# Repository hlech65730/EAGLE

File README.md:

# EAGLE
CAD Repository for PCB Design
- Raspberry Reansas Add On - RRAO1

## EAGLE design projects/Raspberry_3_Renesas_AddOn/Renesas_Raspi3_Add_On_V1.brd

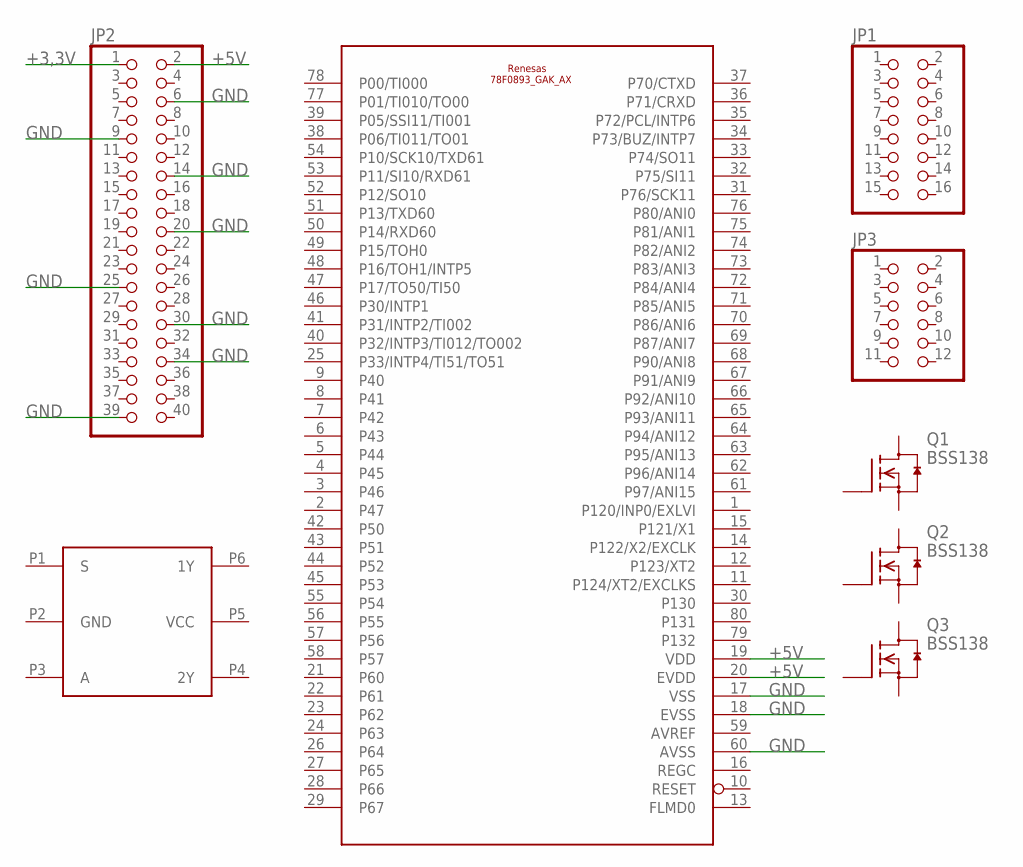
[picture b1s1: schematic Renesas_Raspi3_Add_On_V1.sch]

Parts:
74LVC1G18: 74LVC1G18
78F0893: 78F0893_GAK_AX; LQFP80
JP1: PINHD-2X8; 2X08
JP2: PINHD-2X20; 2X20
JP3: PINHD-2X6; 2X06
Q1, Q2, Q3: BSS138; SOT23

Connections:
+3,3V: JP2.1
+5V: 78F0893.19 (VDD), 78F0893.20 (EVDD), JP2.2
AVREF: 78F0893.59 (AVREF)
GND: 78F0893.17 (VSS), 78F0893.18 (EVSS), 78F0893.60 (AVSS), JP2.6, JP2.9, JP2.14, JP2.20, JP2.25, JP2.30, JP2.34, JP2.39

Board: 2 copper layers, 8 parts (0 on the bottom side), 2 nets, no tracks yet.

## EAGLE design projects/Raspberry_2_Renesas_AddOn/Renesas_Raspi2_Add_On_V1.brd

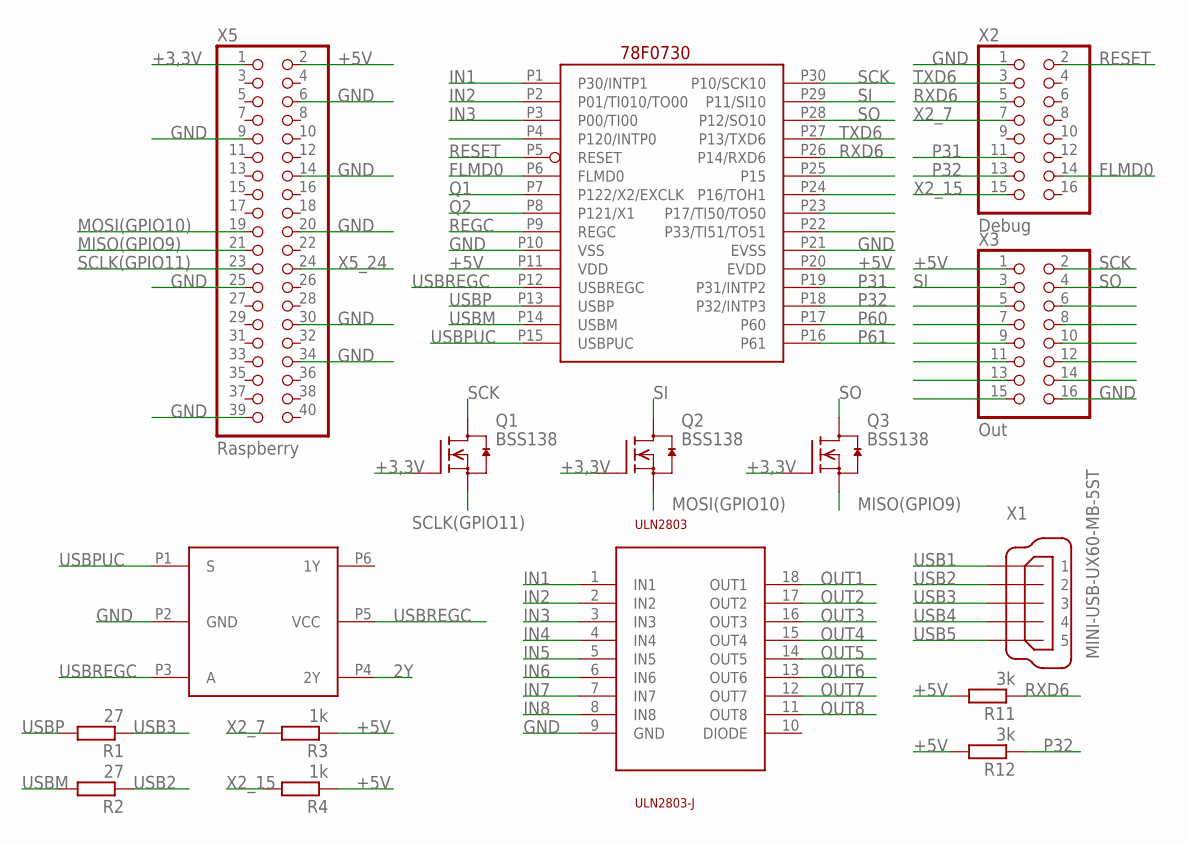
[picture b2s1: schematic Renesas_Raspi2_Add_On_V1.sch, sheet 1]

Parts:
Q1, Q2, Q3: BSS138; SOT23
R1, R2: 27; R0603
R3, R4: 1k; R0603
R11, R12: 3k; R0603
U$1: 78F0730_CAB_AX; SSOP30
U$2: 74LVC1G18
ULN2803: ULN2803-J; SOJ18-45
X1: MINI-USB-UX60-MB-5ST; UX60-MB-5ST
X2: Debug; 2X08
X3: Out; 2X08
X5: Raspberry; 2X20

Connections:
2Y: U$2.P4 (2Y); also elsewhere on the board
+3,3V: Q1.1 (G), Q2.1 (G), Q3.1 (G), X5.1; also elsewhere on the board
+5V: R3.1, R4.1, R11.2, R12.2, U$1.P11 (VDD), U$1.P20 (EVDD), X3.1, X5.2; also elsewhere on the board
FLMD0: U$1.P6 (FLMD0), X2.14
GND: U$1.P10 (VSS), U$1.P21 (EVSS), U$2.P2 (GND), ULN2803.9 (GND), X2.1, X3.16, X5.6, X5.9, X5.14, X5.20, X5.25, X5.30, X5.34, X5.39; also elsewhere on the board
IN1: U$1.P1 (P30/INTP1), ULN2803.1 (IN1)
IN2: U$1.P2 (P01/TI010/TO00), ULN2803.2 (IN2)
IN3: U$1.P3 (P00/TI00), ULN2803.3 (IN3)
IN4: ULN2803.4 (IN4)
IN5: ULN2803.5 (IN5)
IN6: ULN2803.6 (IN6)
IN7: ULN2803.7 (IN7)
IN8: ULN2803.8 (IN8)
MISO(GPIO9): Q3.2 (S), X5.21; also elsewhere on the board
MOSI(GPIO10): Q2.2 (S), X5.19; also elsewhere on the board
OUT1: ULN2803.18 (OUT1)
OUT2: ULN2803.17 (OUT2)
OUT3: ULN2803.16 (OUT3)
OUT4: ULN2803.15 (OUT4)
OUT5: ULN2803.14 (OUT5)
OUT6: ULN2803.13 (OUT6)
OUT7: ULN2803.12 (OUT7)
OUT8: ULN2803.11 (OUT8)
P31: U$1.P19 (P31/INTP2), X2.11
P32: R12.1, U$1.P18 (P32/INTP3), X2.13
P60: U$1.P17 (P60); also elsewhere on the board
P61: U$1.P16 (P61); also elsewhere on the board
Q1: U$1.P7 (P122/X2/EXCLK); also elsewhere on the board
Q2: U$1.P8 (P121/X1); also elsewhere on the board
REGC: U$1.P9 (REGC); also elsewhere on the board
RESET: U$1.P5 (RESET), X2.2; also elsewhere on the board
RXD6: R11.1, U$1.P26 (P14/RXD6), X2.5
SCK: Q1.3 (D), U$1.P30 (P10/SCK10), X3.2; also elsewhere on the board
SCLK(GPIO11): Q1.2 (S), X5.23; also elsewhere on the board
SI: Q2.3 (D), U$1.P29 (P11/SI10), X3.3; also elsewhere on the board
SO: Q3.3 (D), U$1.P28 (P12/SO10), X3.4; also elsewhere on the board
TXD6: U$1.P27 (P13/TXD6), X2.3
USB1: X1.1
USB2: R2.1, X1.2
USB3: R1.1, X1.3; also elsewhere on the board
USB4: X1.4
USB5: X1.5
USBM: R2.2, U$1.P14 (USBM)
USBP: R1.2, U$1.P13 (USBP)
USBPUC: U$1.P15 (USBPUC), U$2.P1 (S)
USBREGC: U$1.P12 (USBREGC), U$2.P3 (A), U$2.P5 (VCC); also elsewhere on the board
X2_7: R3.2, X2.7
X2_15: R4.2, X2.15; also elsewhere on the board
X5_24: X5.24; also elsewhere on the board

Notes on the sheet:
78F0730

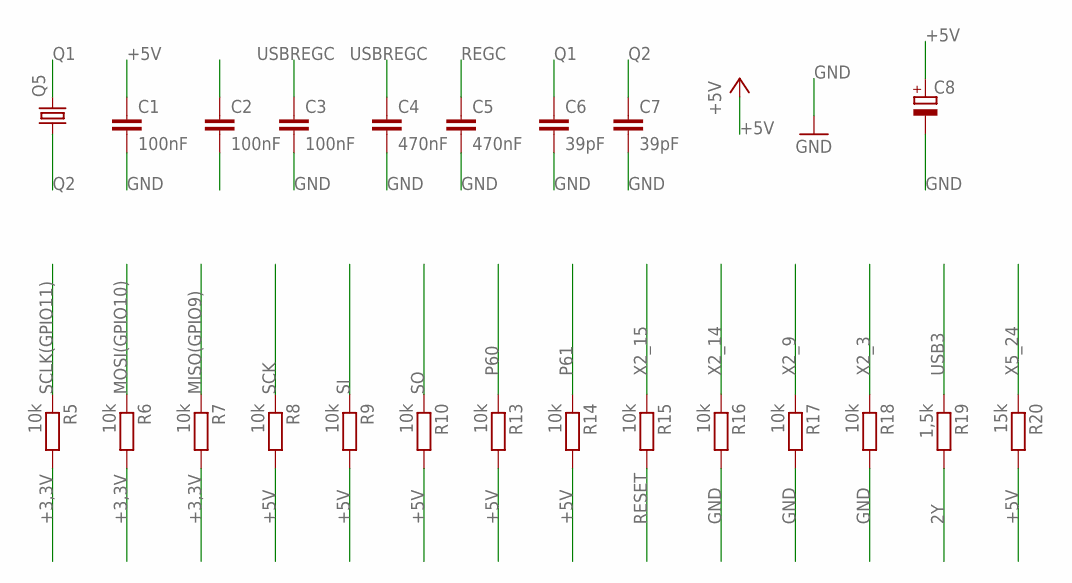
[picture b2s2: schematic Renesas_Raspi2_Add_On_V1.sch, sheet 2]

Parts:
C1, C2, C3: 100nF; C0603
C4, C5: 470nF; C0603
C6, C7: 39pF; C0603
C8: CPOL-EUSANYO_SMD_F8; SANYO-OSCON_SMD_F8
Q5: CRYSTALHC49UP; HC49UP
R5, R6, R7, R8, R9, R10, R13, R14, R15, R16, R17, R18: 10k; R0603
R19: 1,5k; R0603
R20: 15k; R0603

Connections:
2Y: R19.2; also elsewhere on the board
+3,3V: R5.2, R6.2, R7.2; also elsewhere on the board
+5V: C1.1, C8.+, R8.2, R9.2, R10.2, R13.2, R14.2, R20.2; also elsewhere on the board
GND: C1.2, C3.2, C4.2, C5.2, C6.2, C7.2, C8.-, R16.2, R17.2, R18.2; also elsewhere on the board
MISO(GPIO9): R7.1; also elsewhere on the board
MOSI(GPIO10): R6.1; also elsewhere on the board
P60: R13.1; also elsewhere on the board
P61: R14.1; also elsewhere on the board
Q1: C6.1, Q5.2; also elsewhere on the board
Q2: C7.1, Q5.1; also elsewhere on the board
REGC: C5.1; also elsewhere on the board
RESET: R15.2; also elsewhere on the board
SCK: R8.1; also elsewhere on the board
SCLK(GPIO11): R5.1; also elsewhere on the board
SI: R9.1; also elsewhere on the board
SO: R10.1; also elsewhere on the board
USB3: R19.1; also elsewhere on the board
USBREGC: C3.1, C4.1; also elsewhere on the board
X2_3: R18.1
X2_9: R17.1
X2_14: R16.1
X2_15: R15.1; also elsewhere on the board
X5_24: R20.1; also elsewhere on the board

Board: 2 copper layers, 39 parts (0 on the bottom side), 33 nets, no tracks yet.

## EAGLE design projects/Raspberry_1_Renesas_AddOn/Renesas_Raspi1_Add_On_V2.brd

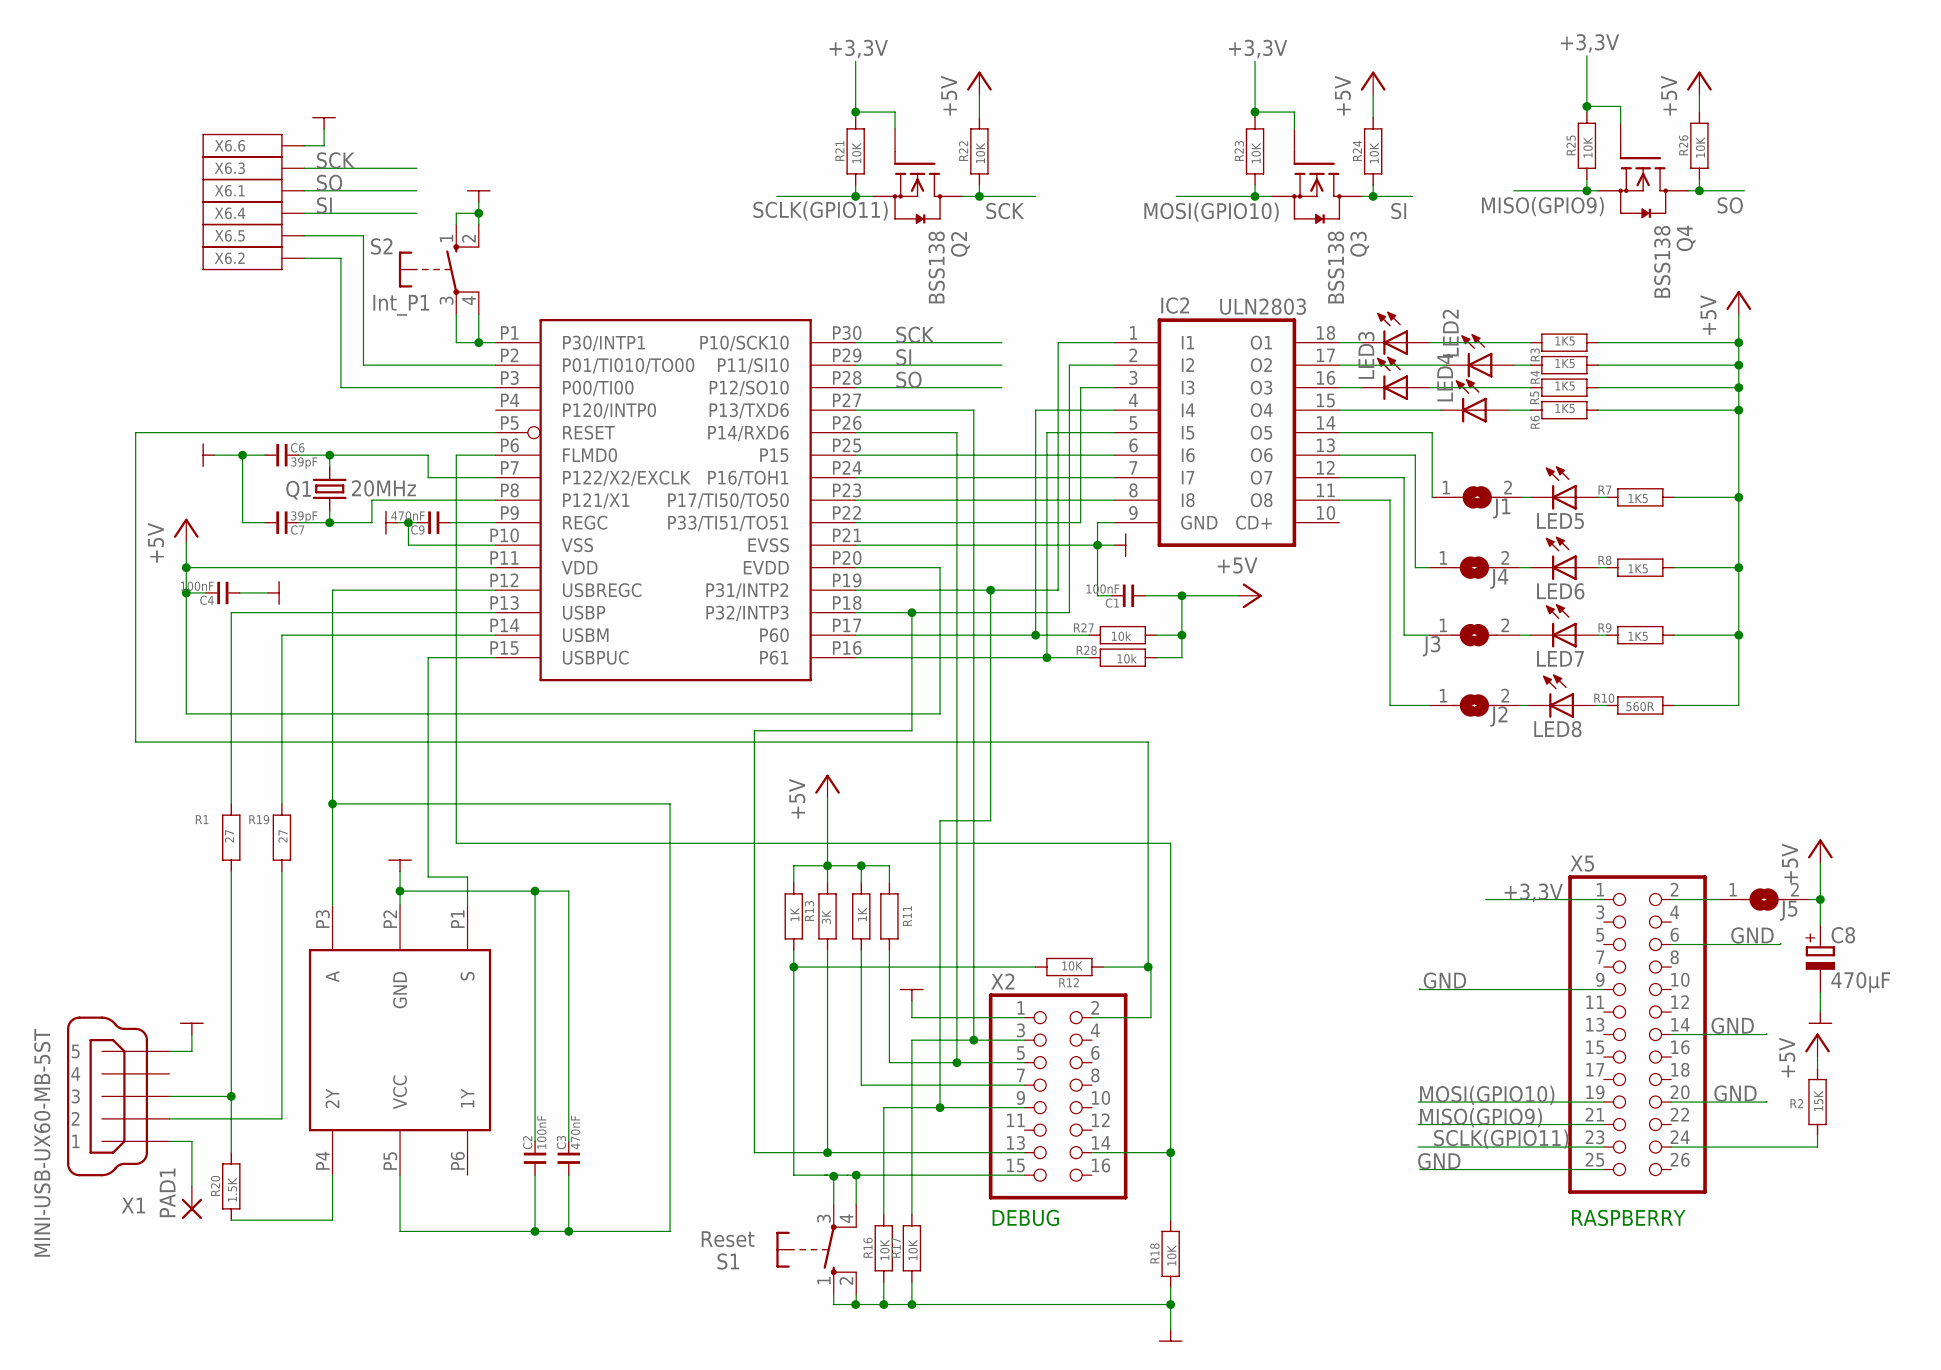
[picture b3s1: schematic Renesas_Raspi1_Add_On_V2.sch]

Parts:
C1, C2, C4: 100nF; 0603
C3, C9: 470nF; 0603
C6, C7: 39pF; 0603
C8: 470µF; SANYO-OSCON_SMD_F8
IC1: 78F0730_CAB_AX; SSOP30
IC2: ULN2803; SOJ18-4
IC3: 74LVC1G18
J1, J2, J3, J4, J5: SJ
LED1, LED2, LED3, LED4, LED5, LED6, LED7, LED8: LEDCHIP-LED0603; CHIP-LED0603
PAD1: 1,6/0,8
Q1: 20MHz; HC49UP
Q2, Q3, Q4: BSS138; SOT23
R1, R19: 27; 0603
R2: 15K; 0603
R3, R4, R5, R6, R7, R8, R9: 1K5; 0603
R10: 560R; 0603
R11, R13: 3K; 0603
R12, R16, R17, R18, R21, R22, R23, R24, R25, R26: 10K; 0603
R14, R15: 1K; 0603
R20: 1.5K; 0603
R27, R28: 10k; 0603
S1: Reset; DT6
S2: Int_P1; DT6
X1: MINI-USB-UX60-MB-5ST; UX60-MB-5ST
X2: PINHD-2X8; 2X08
X5: PINHD-2X13; 2X13
X6: 2X3

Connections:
+3,3V: Q2.1 (G), Q3.1 (G), Q4.1 (G), R21.1, R23.1, R25.1, X5.1
+5V: C1.1, C4.2, C8.+, IC1.P11 (VDD), IC1.P20 (EVDD), J5.2, R2.1, R3.2, R4.2, R5.2, R6.2, R7.1, R8.1, R9.1, R10.1, R11.1, R13.2, R14.1, R15.1, R22.1, R24.1, R26.1, R27.1, R28.1
GND: C1.2, C2.2, C3.2, C4.1, C6.1, C7.1, C8.-, C9.2, IC1.P10 (VSS), IC1.P21 (EVSS), IC2.9 (GND), IC3.P2 (GND), R16.2, R17.2, R18.2, S1.1 (S), S1.2 (S), S2.1 (S), S2.2 (S), X1.5, X2.1, X5.6, X5.9, X5.14, X5.20, X5.25, X6.6
MISO(GPIO9): Q4.2 (S), R25.2, X5.21
MOSI(GPIO10): Q3.2 (S), R23.2, X5.19
unnamed: C7.2, IC1.P8 (P121/X1), Q1.1
unnamed: IC1.P5 (RESET), R12.2, X2.2
unnamed: IC2.18 (O1), LED1.C
unnamed: IC2.17 (O2), LED2.C
unnamed: C6.2, IC1.P7 (P122/X2/EXCLK), Q1.2
unnamed: IC2.16 (O3), LED3.C
unnamed: IC1.P22 (P33/TI51/TO51), IC2.3 (I3)
unnamed: IC1.P17 (P60), IC2.4 (I4), R27.2
unnamed: PAD1.1, X1.1
unnamed: IC1.P19 (P31/INTP2), IC2.1 (I1), R16.1, X2.9
unnamed: IC1.P16 (P61), IC2.5 (I5), R28.2
unnamed: IC1.P25 (P15), IC2.6 (I6)
unnamed: IC1.P24 (P16/TOH1), IC2.7 (I7)
unnamed: R12.1, R15.2, S1.3, S1.4, X2.15
unnamed: IC1.P23 (P17/TI50/TO50), IC2.8 (I8)
unnamed: R2.2, X5.24
unnamed: LED1.A, R3.1
unnamed: IC2.15 (O4), LED4.C
unnamed: J5.1, X5.2
unnamed: R14.2, X2.7
unnamed: LED2.A, R4.1
unnamed: LED3.A, R5.1
unnamed: IC1.P1 (P30/INTP1), S2.3, S2.4
unnamed: LED4.A, R6.1
unnamed: LED8.A, R10.2
unnamed: IC1.P2 (P01/TI010/TO00), X6.5
unnamed: IC1.P3 (P00/TI00), X6.2
unnamed: IC2.13 (O6), J4.1
unnamed: C9.1, IC1.P9 (REGC)
unnamed: J1.2, LED5.C
unnamed: IC2.12 (O7), J3.1
unnamed: LED7.A, R9.2
unnamed: IC2.11 (O8), J2.1
unnamed: LED6.A, R8.2
unnamed: LED5.A, R7.2
unnamed: IC1.P6 (FLMD0), R18.1, X2.14
unnamed: IC1.P18 (P32/INTP3), IC2.2 (I2), R13.1, X2.13
unnamed: IC1.P13 (USBP), R1.1
unnamed: R1.2, R20.1, X1.3
unnamed: R19.2, X1.2
unnamed: IC1.P14 (USBM), R19.1
unnamed: IC1.P15 (USBPUC), IC3.P1 (S)
unnamed: C2.1, C3.1, IC1.P12 (USBREGC), IC3.P3 (A), IC3.P5 (VCC)
unnamed: IC3.P4 (2Y), R20.2
unnamed: J4.2, LED6.C
unnamed: J3.2, LED7.C
unnamed: J2.2, LED8.C
unnamed: IC2.14 (O5), J1.1
unnamed: IC1.P26 (P14/RXD6), R11.2, X2.5
unnamed: IC1.P27 (P13/TXD6), R17.1, X2.3
SCK: IC1.P30 (P10/SCK10), Q2.3 (D), R22.2, X6.3
SCLK(GPIO11): Q2.2 (S), R21.2, X5.23
SI: IC1.P29 (P11/SI10), Q3.3 (D), R24.2, X6.4
SO: IC1.P28 (P12/SO10), Q4.3 (D), R26.2, X6.1

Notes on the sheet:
DEBUG
RASPBERRY

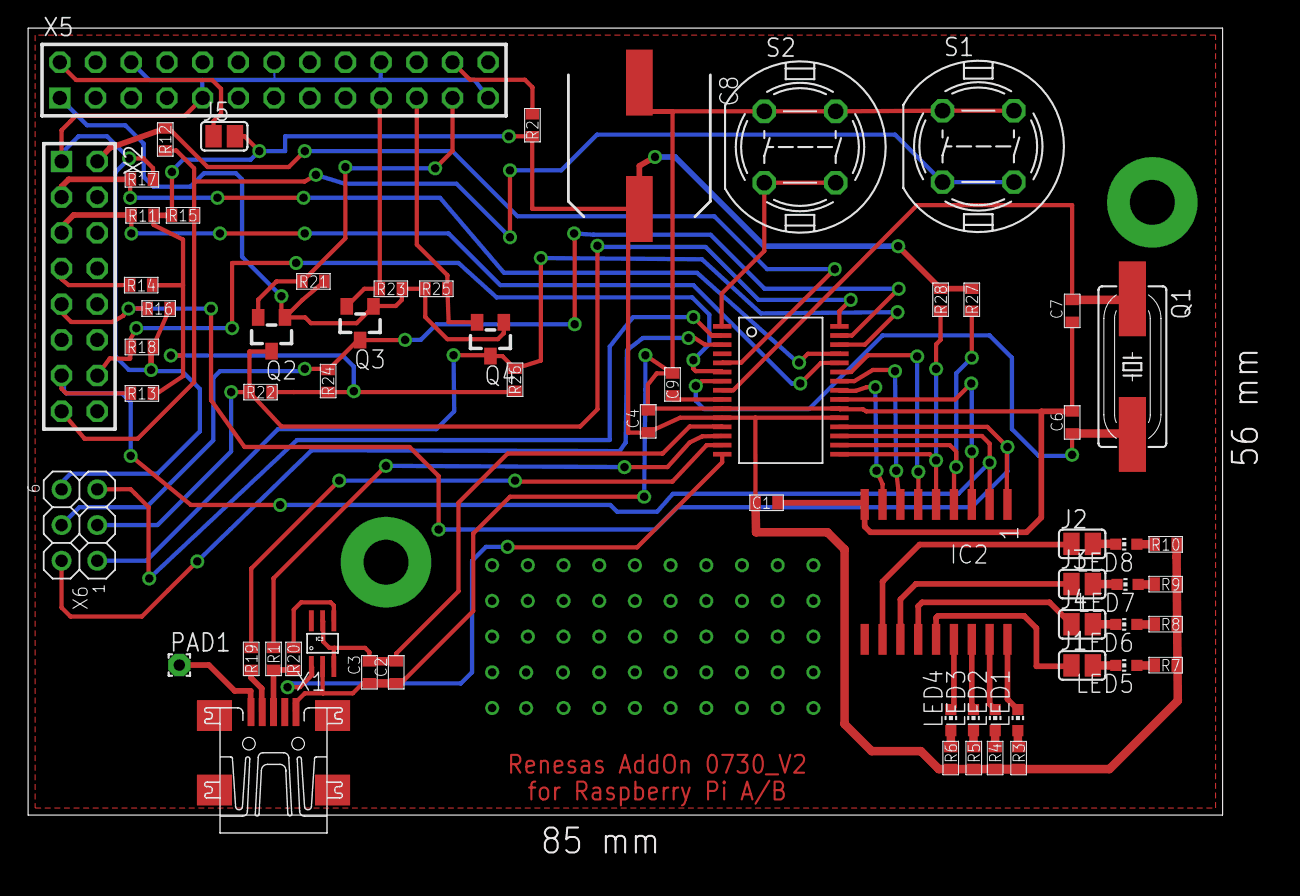
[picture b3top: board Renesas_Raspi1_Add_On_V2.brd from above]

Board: 2 copper layers, 88.5 x 59.7 mm, 63 parts (0 on the bottom side), 59 nets.

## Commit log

2022-02-05 Create LICENSE
2022-02-06 First EAGLE commit for Projects Renesas_Raspi(1_2_3)Add_On Boards

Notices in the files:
parts and their libraries:
m-pad-2.1: License : GNU General Public License version 2 (see bottom)
